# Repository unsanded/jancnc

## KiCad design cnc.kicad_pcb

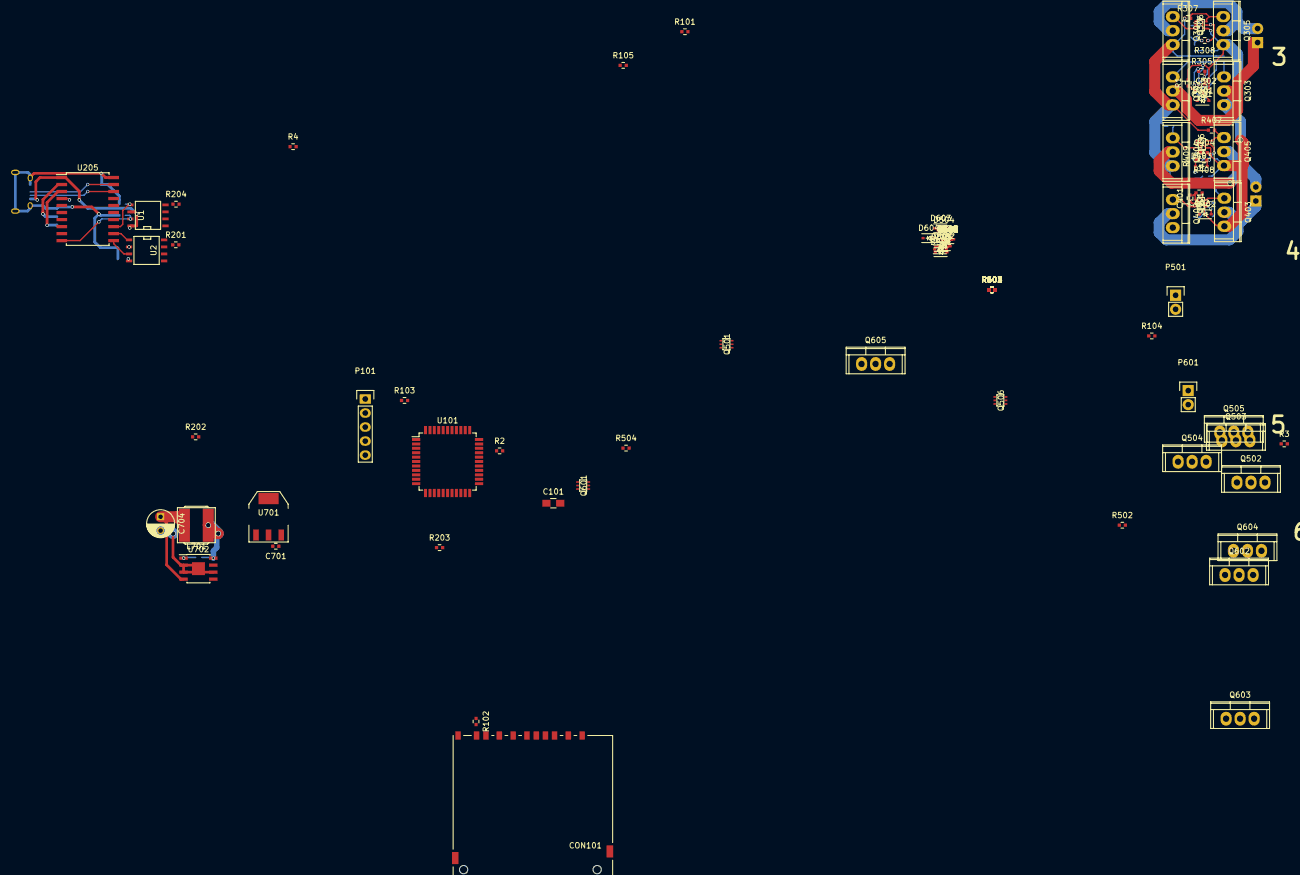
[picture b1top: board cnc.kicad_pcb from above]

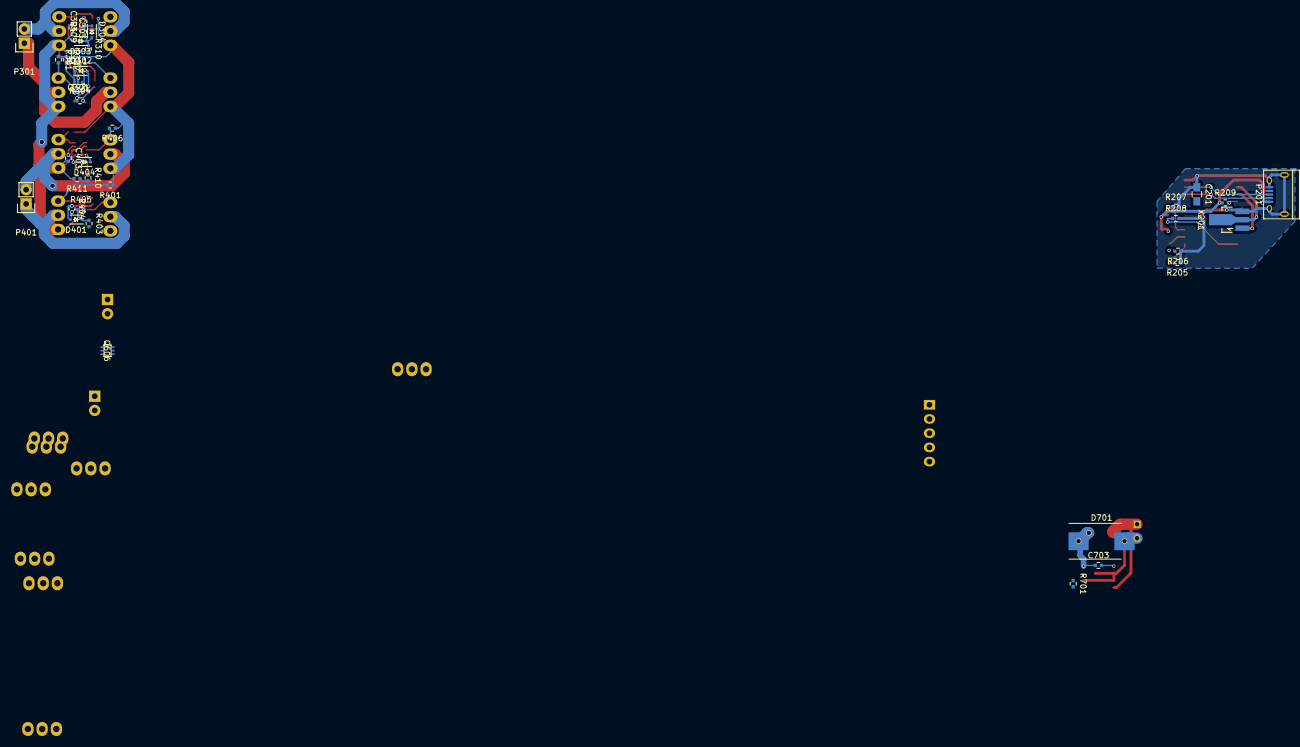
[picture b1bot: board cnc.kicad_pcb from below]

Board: 2 copper layers, 141 parts (36 on the bottom side), 94 nets.

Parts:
C101: 1uF; C_0805_HandSoldering
C201: C; C_0805_HandSoldering
C301, C302, C303, C304, C401, C402, C403, C404, C501, C502, C503, C504, C601, C602, C603, C604: 15nF; R_0402_handsoldering
C701: 100nF; R_0402_handsoldering
C702: 10uF; R_0402_handsoldering
C703: 10nF; R_0402_handsoldering
C704: 120uF; C_Radial_D5_L11_P2.5
CON101: SD_Card; SD_Card_Receptacle
D301, D302, D303, D304, D401, D402, D403, D404, D501, D502, D503, D504, D601, D602, D603, D604: D; SOD-323
D701: D_Schottky; DO-214AB_Handsoldering
L701: 15uH; VLS6045EX_6x6
P101: icsp; Pin_Header_Straight_1x05
P201: USB_OTG; USB_Micro-B
P301, P401, P501, P601: CONN_01X02; Pin_Header_Straight_1x02
Q301, Q306, Q401, Q406, Q501, Q506, Q601, Q606: NTJD5121N; SOT-363
Q302, Q304, Q402, Q404, Q502, Q504, Q602, Q604: IRF4905PbF; TO-220
Q303, Q305, Q403, Q405, Q503, Q505, Q603, Q605: FQP85N06; TO-220
R1, R2, R3, R4, R101, R201, R202, R301, R302, R306, R307, R311, R401, R402, R406, R407, R411, R501, R502, R506, R507, R511, R601, R602, R606, R607, R611: 10k; R_0402_handsoldering
R102, R103, R104, R105: 50k; R_0402_handsoldering
R203, R204, R205, R206, R207, R208, R209: R; R_0402_handsoldering
R303, R310, R403, R410, R503, R510, R603, R610: 30R; R_0402_handsoldering
R304, R305, R308, R309, R404, R405, R408, R409, R504, R505, R508, R509, R604, R605, R608, R609: 1k; R_0402_handsoldering
R701: 500k; R_0402_handsoldering
U1, U2: ACPL-227; SOIC-8-N
U101: pic32; TQFP-44_10x10mm_Pitch0.8mm
U205: MCP2200; SOIC-20_7.5x12.8mm_Pitch1.27mm
U701: LD1117S33TR; SOT-223
U702: LM22676; SOIC-8-1EP_3.9x4.9mm_Pitch1.27mm
X201: CRYSTAL_SMD; SOT89-3_Housing_Handsoldering

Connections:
+3V3: C702.1, CON101.4, P101.2, R101.2, R102.1, R103.1, R104.1, R105.1, U2.6, U2.8, U101.28, U101.40, U701.2
+5V: C701.1, C704.1, L701.2, U701.3, U702.4
/SD_Din: CON101.2, U101.11
/SD_Dout: CON101.7, R103.2, U101.44
/SD_clk: CON101.5, U101.14
/hbridge1/INA: R1.1, R303.2, U101.19
/hbridge1/INB: R310.2, R311.1, U101.20
/hbridge2/INA: R2.1, R403.2, U101.30
/hbridge2/INB: R410.2, R411.1, U101.31
/hbridge3/INA: R3.1, R503.2, U101.21
/hbridge3/INB: R510.2, R511.1, U101.22
/hbridge4/INA: R4.1, R603.2, U101.23
/hbridge4/INB: R610.2, R611.1, U101.24
/pgec: P101.5, U101.9
/pged: P101.4, U101.8
/uart/CTS: U1.3, U101.27
/uart/RTS: R202.1, U2.5, U101.41
/uart/RX: R201.1, U2.7, U101.25
/uart/TX: U1.1, U101.26
/uart/V_USB: P201.1, R209.1, U1.6, U1.8, U205.1
GND: C101.2, C701.2, C702.2, C704.2, CON101.3, CON101.6, CON101.12, CON101.13, D701.2, P101.3, R201.2, R202.2, R203.2, R204.2, U101.6, U101.29, U101.39, U701.1, U702.2, U702.3, U702.6, U702.9
GND_USB: C201.1, P201.5, P201.6, R205.1, R206.1, R207.2, R208.2, U205.20, X201.3
unnamed: C101.1, U101.7
unnamed: C201.2, U205.17
unnamed: C301.1, D302.1, Q301.5, R305.2
unnamed: C302.1, D301.2, Q301.2, R304.1
unnamed: C303.1, D303.2, Q306.2, R308.1
unnamed: C304.1, D304.1, Q306.5, R309.2
unnamed: C401.1, D402.1, Q401.5, R405.2
unnamed: C402.1, D401.2, Q401.2, R404.1
unnamed: C403.1, D403.2, Q406.2, R408.1
unnamed: C404.1, D404.1, Q406.5, R409.2
unnamed: C501.1, D502.1, Q501.5, R505.2
unnamed: C502.1, D501.2, Q501.2, R504.1
unnamed: C503.1, D503.2, Q506.2, R508.1
unnamed: C504.1, D504.1, Q506.5, R509.2
unnamed: C601.1, D602.1, Q601.5, R605.2
unnamed: C602.1, D601.2, Q601.2, R604.1
unnamed: C603.1, D603.2, Q606.2, R608.1
unnamed: C604.1, D604.1, Q606.5, R609.2
unnamed: C703.1, D701.1, L701.1, U702.8
unnamed: C703.2, U702.1
unnamed: CON101.1, R104.2
unnamed: CON101.8, R102.2
unnamed: CON101.9, R105.2
unnamed: D301.1, D302.2, R303.1, R304.2, R305.1
unnamed: D303.1, D304.2, R308.2, R309.1, R310.1
unnamed: D401.1, D402.2, R403.1, R404.2, R405.1
unnamed: D403.1, D404.2, R408.2, R409.1, R410.1
unnamed: D501.1, D502.2, R503.1, R504.2, R505.1
unnamed: D503.1, D504.2, R508.2, R509.1, R510.1
unnamed: D601.1, D602.2, R603.1, R604.2, R605.1
unnamed: D603.1, D604.2, R608.2, R609.1, R610.1
unnamed: P101.1, R101.1, U101.18
unnamed: P201.2, U205.18
unnamed: P201.3, U205.19
unnamed: P301.1, Q302.2, Q303.2
unnamed: P301.2, Q304.2, Q305.2
unnamed: P401.1, Q402.2, Q403.2
unnamed: P401.2, Q404.2, Q405.2
unnamed: P501.1, Q502.2, Q503.2
unnamed: P501.2, Q504.2, Q505.2
unnamed: P601.1, Q602.2, Q603.2
unnamed: P601.2, Q604.2, Q605.2
unnamed: Q301.3, Q303.1, R301.2
unnamed: Q301.6, Q302.1, R302.2
unnamed: Q304.1, Q306.6, R306.2
unnamed: Q305.1, Q306.3, R307.2
unnamed: Q401.3, Q403.1, R401.2
unnamed: Q401.6, Q402.1, R402.2
unnamed: Q404.1, Q406.6, R406.2
unnamed: Q405.1, Q406.3, R407.2
unnamed: Q501.3, Q503.1, R501.2
unnamed: Q501.6, Q502.1, R502.2
unnamed: Q504.1, Q506.6, R506.2
unnamed: Q505.1, Q506.3, R507.2
unnamed: Q601.3, Q603.1, R601.2
unnamed: Q601.6, Q602.1, R602.2
unnamed: Q604.1, Q606.6, R606.2
unnamed: Q605.1, Q606.3, R607.2
unnamed: R203.1, U1.2
unnamed: R204.1, U1.4
unnamed: R205.2, U2.4
unnamed: R206.2, U2.2
unnamed: R207.1, U1.5, U205.13
unnamed: R208.1, U1.7, U205.10
unnamed: R209.2, U205.4
unnamed: R701.2, U702.5
unnamed: U2.1, U205.12
unnamed: U2.3, U205.11
unnamed: U205.2, X201.2
unnamed: U205.3, X201.1
PWR_GND: C301.2, C302.2, C303.2, C304.2, C401.2, C402.2, C403.2, C404.2, C501.2, C502.2, C503.2, C504.2, C601.2, C602.2, C603.2, C604.2, Q301.1, Q301.4, Q303.3, Q305.3, Q306.1, Q306.4, Q401.1, Q401.4, Q403.3, Q405.3, Q406.1, Q406.4, Q501.1, Q501.4, Q503.3, Q505.3, Q506.1, Q506.4, Q601.1, Q601.4, Q603.3, Q605.3, Q606.1, Q606.4, R1.2, R2.2, R3.2, R4.2, R311.2, R411.2, R511.2, R611.2
Vpower: Q302.3, Q304.3, Q402.3, Q404.3, Q502.3, Q504.3, Q602.3, Q604.3, R301.1, R302.1, R306.1, R307.1, R401.1, R402.1, R406.1, R407.1, R501.1, R502.1, R506.1, R507.1, R601.1, R602.1, R606.1, R607.1, R701.1, U702.7

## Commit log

2016-06-28 Initial commit
    Has
    - galvanicly insulated uart.
    - one h-bridge
    - sd-card slot
2016-06-29 added 3 more h-bridges, and routed a bit
2016-08-24 Added requirements
    Also selected components for certain things.
2016-08-24 Routed a h-bridge. Damn that's a lot of work.
    also assigned a lot of components.
2016-09-05 added requirements.
